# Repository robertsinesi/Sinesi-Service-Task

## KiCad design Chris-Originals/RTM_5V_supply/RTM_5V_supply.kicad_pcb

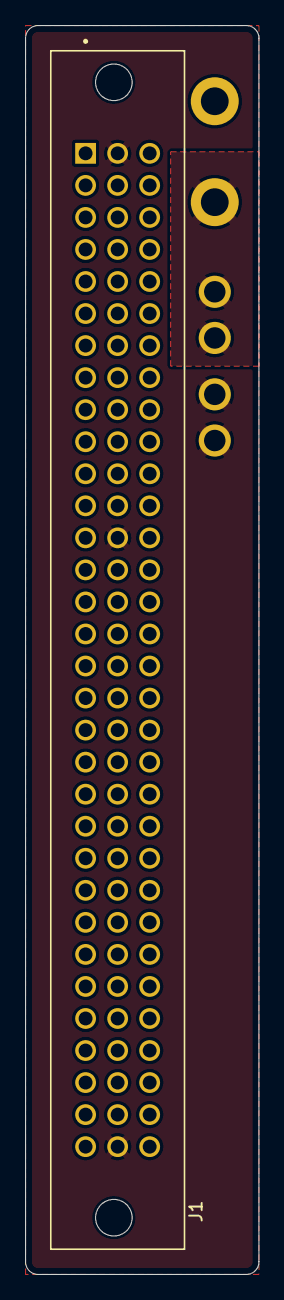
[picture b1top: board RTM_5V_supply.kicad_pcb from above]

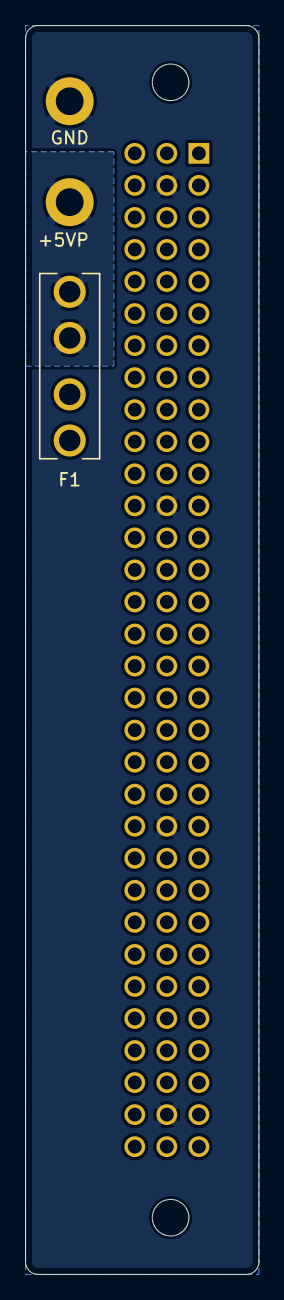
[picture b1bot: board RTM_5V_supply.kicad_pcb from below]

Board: 4 copper layers, 18.5 x 99.0 mm, 4 parts (3 on the bottom side), 3 nets, no tracks yet.

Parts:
+5VP: MountingHole_Pad; PTH_12AWG
F1: 3544-2; FUSE_3544-2
GND: MountingHole_Pad; PTH_12AWG
J1: 86093968114755V1LF; AMPHENOL_86093968114755V1LF

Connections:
+5V: F1.1_1, F1.1_2, J1.B1, J1.B13, J1.B32
+5VP: +5VP.1, F1.2_1, F1.2_2
GND: GND.1, J1.B2, J1.B12, J1.B22, J1.B31
